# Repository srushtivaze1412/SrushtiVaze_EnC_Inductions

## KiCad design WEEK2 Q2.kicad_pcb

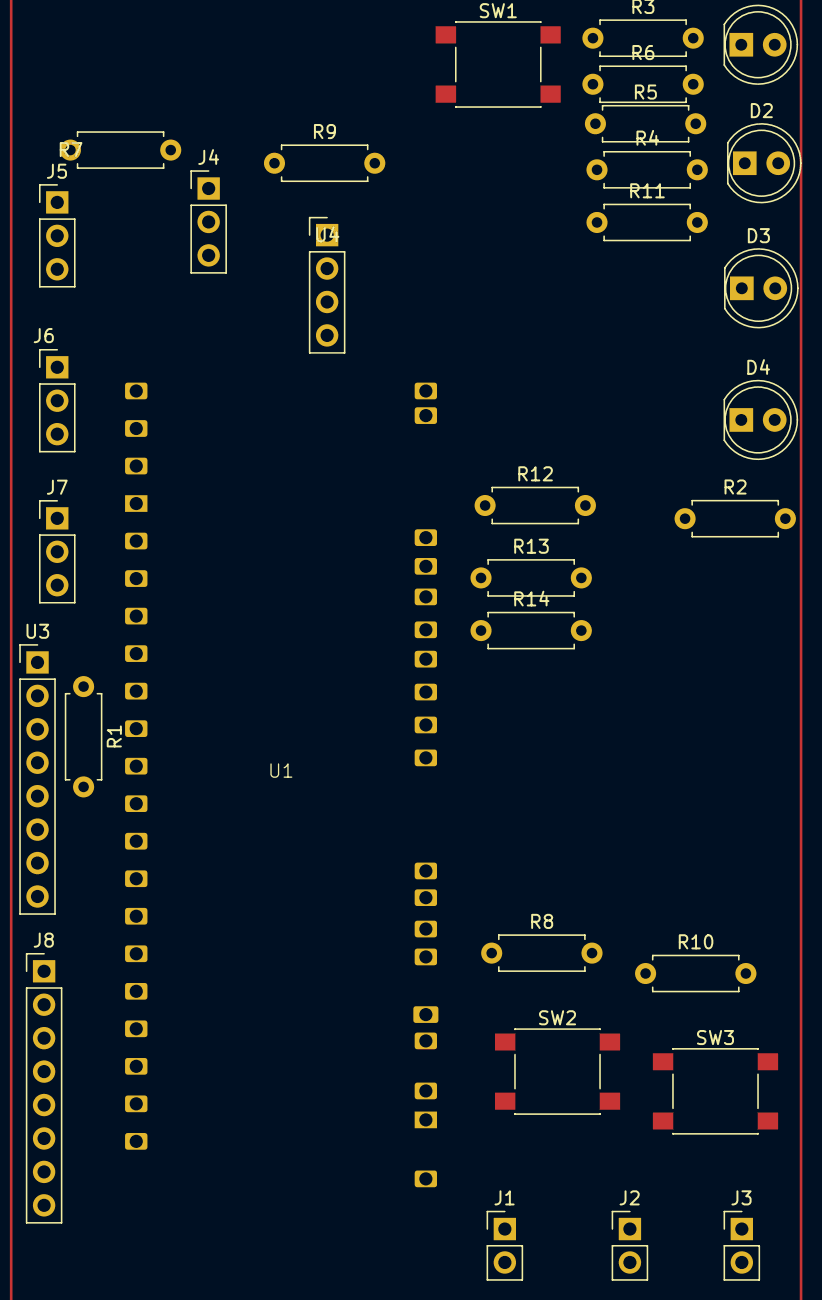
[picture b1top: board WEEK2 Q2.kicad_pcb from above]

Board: 2 copper layers, 32 parts (0 on the bottom side), 35 nets, no tracks yet.

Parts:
D1, D2, D3, D4: LED; LED_D5.0mm
J1, J2, J3: Conn_01x02_Pin; PinHeader_1x02_P2.54mm_Vertical
J4, J5, J6, J7: Conn_01x03_Pin; PinHeader_1x03_P2.54mm_Vertical
J8: Conn_01x08_Pin; PinHeader_1x08_P2.54mm_Vertical
R1, R2, R11, R12, R13, R14: R; R_Axial_DIN0207_L6.3mm_D2.5mm_P7.62mm_Horizontal
R3, R4, R8, R10: 10k; R_Axial_DIN0207_L6.3mm_D2.5mm_P7.62mm_Horizontal
R5, R6, R7, R9: 20k; R_Axial_DIN0207_L6.3mm_D2.5mm_P7.62mm_Horizontal
SW1, SW2, SW3: SW_SPST; SW_SPST_PTS645
U1: ESP32-S3-DEVKITC-1U-N8R8; ESP32S3U1DevKitN8R2
U3: PinHeader_1x08_P2.54mm_Vertical
U4: PinHeader_1x04_P2.54mm_Vertical

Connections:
+3.3V: R1.1, R2.1, U1.J1_1 (3V3), U3.1 (VCC)
+5V: J4.2, J5.2, J6.2, J7.2, SW1.2 (B), SW2.2 (B), SW3.2 (B), U4.4 (VCC)
/SCL: R2.2, U1.J1_15 (GPIO9), U3.3 (SCL)
/SDA: R1.2, U1.J1_12 (GPIO8), U3.4 (SDA)
/SERVO1: J4.3, U1.J3_14 (GPIO0)
/SERVO2: J5.3, U1.J3_4 (GPIO1)
/SERVO3: J6.3, U1.J3_5 (GPIO2)
/SERVO4: J7.3, U1.J1_13 (GPIO3)
GND: D1.1 (K), D2.1 (K), D3.1 (K), D4.1 (K), J1.2, J2.2, J3.2, J4.1, J5.1, J6.1, J7.1, R3.2, R4.2, R8.2, R10.2, U1.J1_22 (GND), U3.2 (GND), U3.7 (ADO), U4.1 (GND)
unnamed: D1.2 (A), R11.2
unnamed: D2.2 (A), R12.2
unnamed: D3.2 (A), R13.2
unnamed: D4.2 (A), R14.2
unnamed: J1.1, R3.1, R6.1, SW1.1 (A)
unnamed: J2.1, R7.1, R8.1, SW2.1 (A)
unnamed: J3.1, R9.1, R10.1, SW3.1 (A)
unnamed: J8.1, U1.J1_18 (GPIO12)
unnamed: J8.2, U1.J1_19 (GPIO13)
unnamed: J8.3, U1.J1_20 (GPIO14)
unnamed: J8.4, U1.J1_8 (GPIO15)
unnamed: J8.5, U1.J1_9 (GPIO16)
unnamed: J8.6, U1.J1_10 (GPIO17)
unnamed: J8.7, U1.J1_11 (GPIO18)
unnamed: J8.8, U1.J3_18 (GPIO21)
unnamed: R11.1, U1.J3_13 (GPIO35)
unnamed: R12.1, U1.J3_12 (GPIO36)
unnamed: R13.1, U1.J3_11 (GPIO37)
unnamed: R14.1, U1.J3_10 (GPIO38)
unnamed: U1.J3_7 (MTDI/GPIO41), U3.8 (INT)
unnamed: U1.J3_6 (MTMS/GPIO42), U4.3 (TRIG)
unnamed: R6.2, U1.J3_3 (U0RXD/GPIO44)
unnamed: R5.2, U1.J3_2 (U0TXD/GPIO43)
unnamed: R9.2, U1.J3_19 (USB_D+/GPIO20)
unnamed: R7.2, U1.J3_20 (USB_D-/GPIO19)
unnamed: R4.1, R5.1, U4.2 (ECHO)
